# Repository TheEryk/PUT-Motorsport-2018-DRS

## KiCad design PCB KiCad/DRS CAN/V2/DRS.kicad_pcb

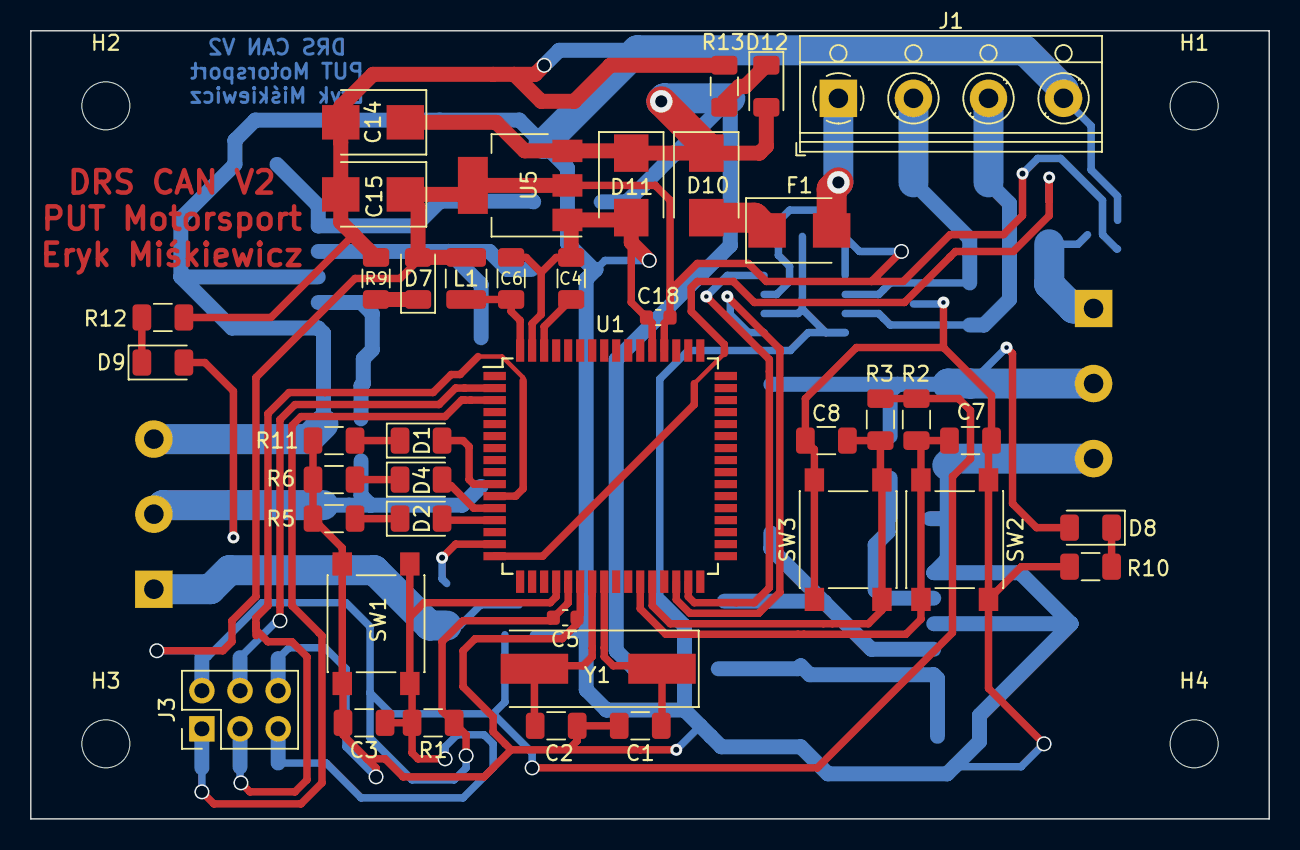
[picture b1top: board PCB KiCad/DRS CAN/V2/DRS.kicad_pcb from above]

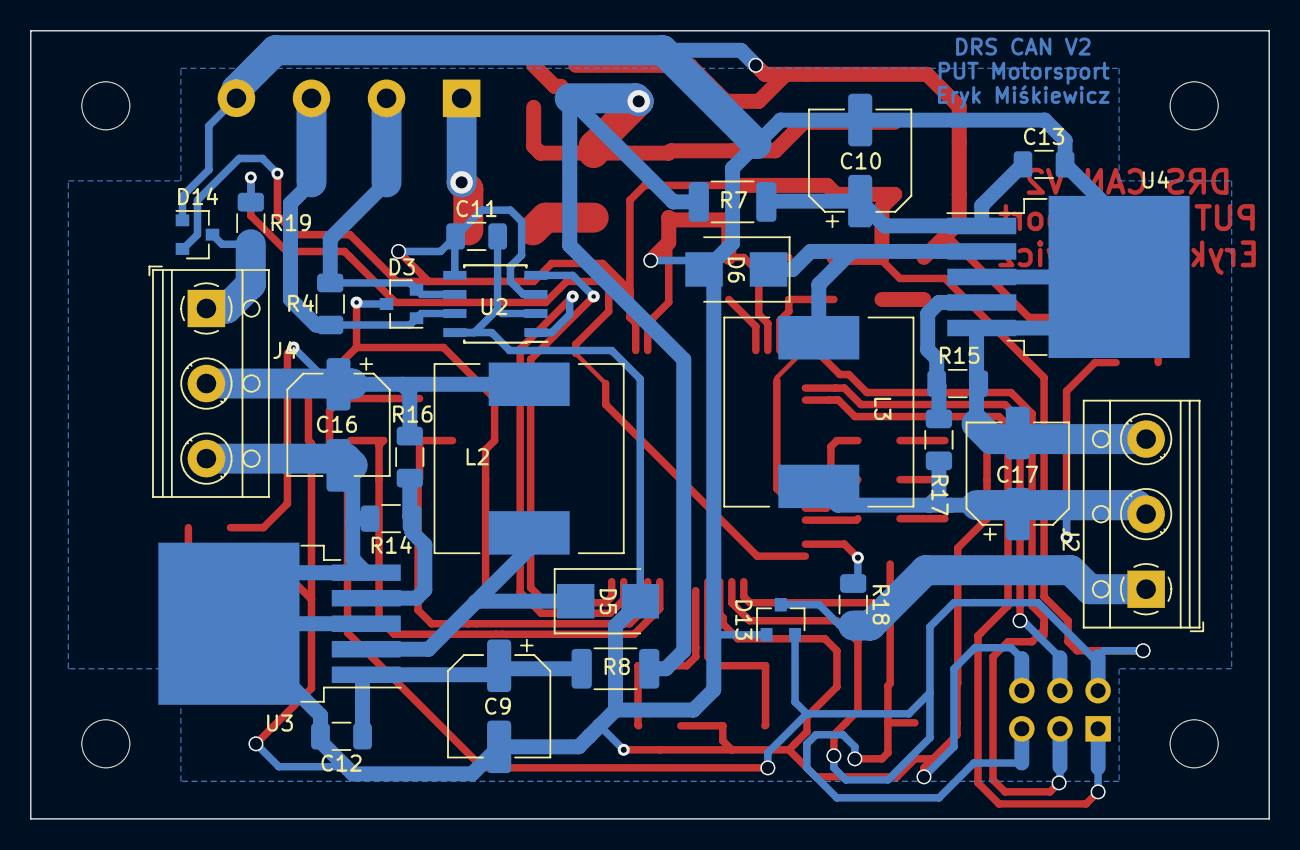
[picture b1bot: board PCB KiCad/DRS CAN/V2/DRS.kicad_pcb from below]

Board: 2 copper layers, 82.5 x 52.5 mm, 72 parts (28 on the bottom side), 41 nets.

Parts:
C1, C2: 22p; C_1206_3216Metric
C3, C4, C6, C7, C8, C11, C12, C13: 100n; C_1206_3216Metric
C5, C18: 100n; C_0603_1608Metric
C9, C10: 100u; CP_Elec_6.3x7.7
C14, C15: CP; D_SMB
C16, C17: 220u; CP_Elec_6.3x7.7
D1, D2, D4, D7, D8, D9, D12: LED; LED_1206_3216Metric
D3: D_TVS_x2_AAC; SOT-23
D5, D6, D10: D_Schottky; D_SMB
D11: D_Zener; D_SMB
D13, D14: BAT54S; SOT-23
F1: Fuse; D_SMB
H1, H2, H3, H4: MountingHole; MountingHole_3.2mm_M3
J1: Screw_Terminal_01x04; TerminalBlock_RND_205-00014_1x04_P5.00mm_Horizontal
J2, J4: Screw_Terminal_01x03; TerminalBlock_RND_205-00013_1x03_P5.00mm_Horizontal
J3: Conn_02x03_Odd_Even; PinHeader_2x03_P2.54mm_Vertical
L1: 10u; L_1210_3225Metric
L2, L3: 33u; L_12x12mm_H8mm
R1, R2, R3: 10k; R_1206_3216Metric
R4: R_Small; R_1206_3216Metric
R5, R6, R9, R10, R11, R12: 330; R_1206_3216Metric
R7, R8: 0R; R_2010_5025Metric
R13: 2k; R_1206_3216Metric
R14, R15, R16, R17: 0R; R_1206_3216Metric
R18, R19: 1k; R_1206_3216Metric
SW1, SW2, SW3: SW_Push; SW_SPST_PTS645
U1: AT90CAN32-16AU; TQFP-64_14x14mm_P0.8mm
U2: MCP2562-E-SN; SOIC-8_3.9x4.9mm_P1.27mm
U3, U4: AP1501-K5G-13; TO-263-5_TabPin3
U5: LM1117-5.0; SOT-223-3_TabPin2
Y1: Crystal; Crystal_SMD_HC49-SD

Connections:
+5V: C5.2, C11.1, C15.1, C18.2, D7.2, D13.2, D14.2, J3.2, L1.1, R1.1, R2.1, R3.1, U1.21, U1.52, U2.3, U2.5, U5.2
+5VL: C17.1, D9.2, J2.2, L3.2, R17.2
+5VP: C16.1, D8.2, J4.2, L2.2, R16.2
+12P: F1.2, J1.1
+12V: C14.1, D10.1, D11.1, D12.2, R7.2, R8.2, U5.3
/Button1: C7.2, R2.2, SW2.2, U1.27
/Button2: C8.2, R3.2, SW3.2, U1.28
/CANH: D3.1, J1.3, R4.1, U2.7
/CANL: D3.2, J1.2, R4.2, U2.6
/LED1: D1.2, U1.10
/LED2: D4.2, U1.12
/LED3: D2.2, U1.13
/MISO: J3.1, U1.3
/MOSI: J3.4, U1.2
/PWM1: R18.1, U1.15
/PWM2: R19.1, U1.16
/RESET: C3.1, J3.5, R1.2, SW1.2, U1.20
/RXCAN: U1.31, U2.4
/SCK: J3.3, U1.11
/TXCAN: U1.30, U2.1
/Zasilanie/5LU: D6.1, L3.1, U4.2
/Zasilanie/5PU: D5.1, L2.1, U3.2
/Zasilanie/12L: C10.1, C13.1, R7.1, U4.1
/Zasilanie/12P: C9.1, C12.1, R8.1, U3.1
/Złącza/PWM1Out: D13.3, J2.1, R18.2
/Złącza/PWM2Out: D14.3, J4.1, R19.2
GND: C1.2, C2.2, C3.2, C4.2, C5.1, C6.1, C7.1, C8.1, C9.2, C10.2, C11.2, C12.2, C13.2, C14.2, C15.2, C16.2, C17.2, C18.1, D3.3, D5.2, D6.2, D11.2, D13.1, D14.1, J1.4, J2.3, J3.6, J4.3, R5.2, R6.2, R9.2, R10.2, R11.2, R12.2, R13.2, R14.1, R15.1, SW1.1, SW2.1, SW3.1, U1.22, U1.53, U1.63, U2.2, U2.8, U3.3, U3.5, U4.3, U4.5, U5.1
unnamed: C1.1, U1.24, Y1.1
unnamed: C2.1, U1.23, Y1.2
unnamed: C4.1, U1.62
unnamed: C6.2, L1.2, U1.64
unnamed: D1.1, R11.1
unnamed: D2.1, R5.1
unnamed: D4.1, R6.1
unnamed: D7.1, R9.1
unnamed: D8.1, R10.1
unnamed: D9.1, R12.1
unnamed: D10.2, F1.1
unnamed: D12.1, R13.1
unnamed: R14.2, R16.1, U3.4
unnamed: R15.2, R17.1, U4.4

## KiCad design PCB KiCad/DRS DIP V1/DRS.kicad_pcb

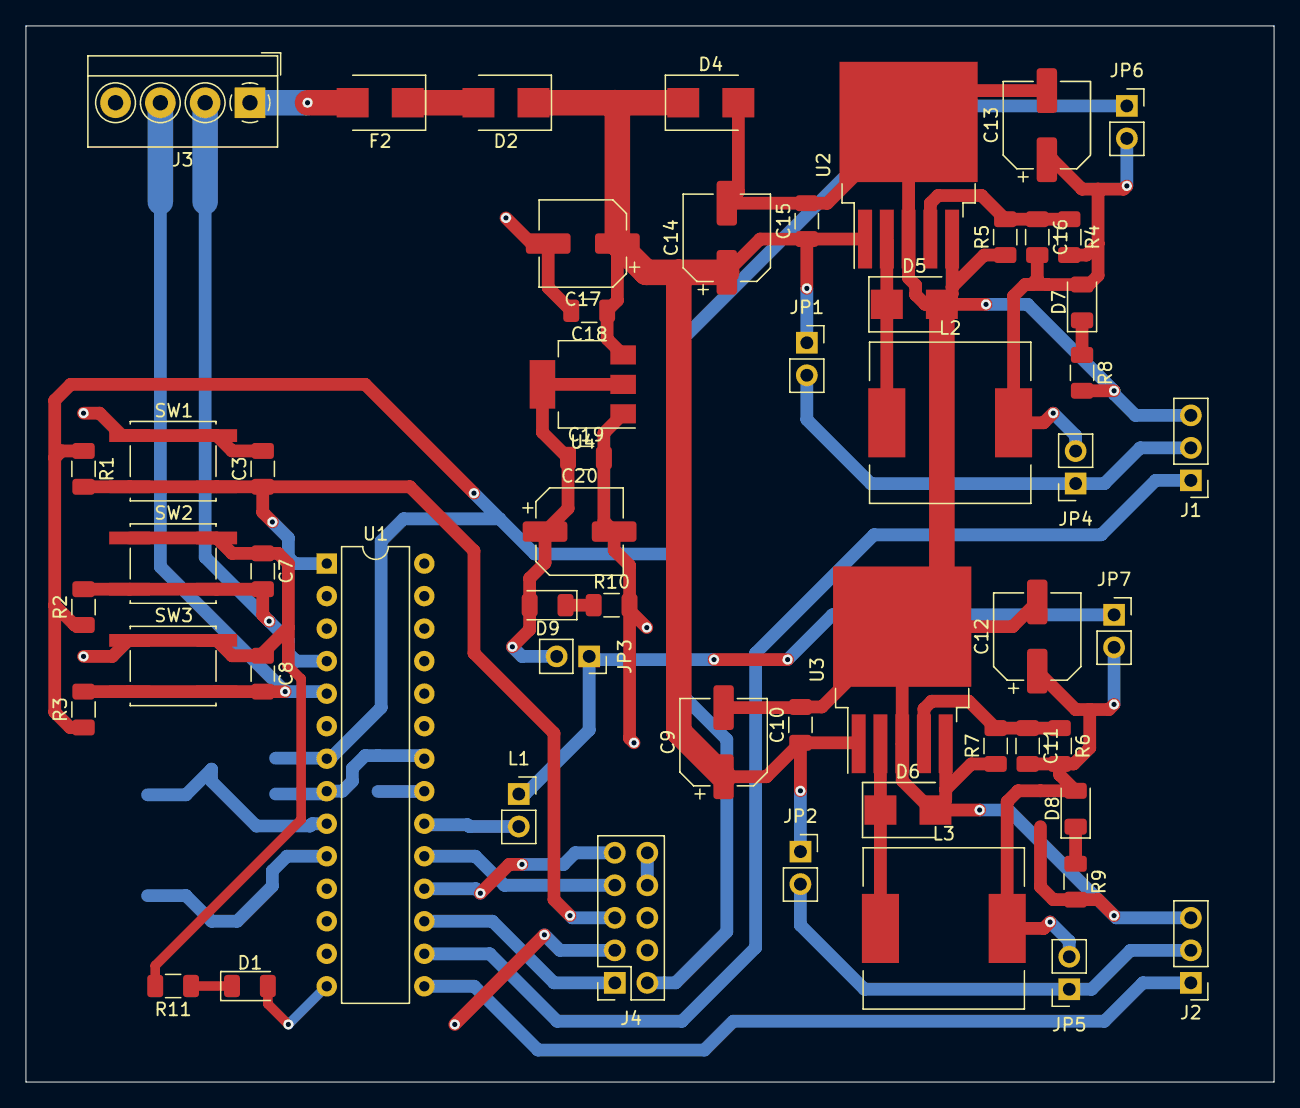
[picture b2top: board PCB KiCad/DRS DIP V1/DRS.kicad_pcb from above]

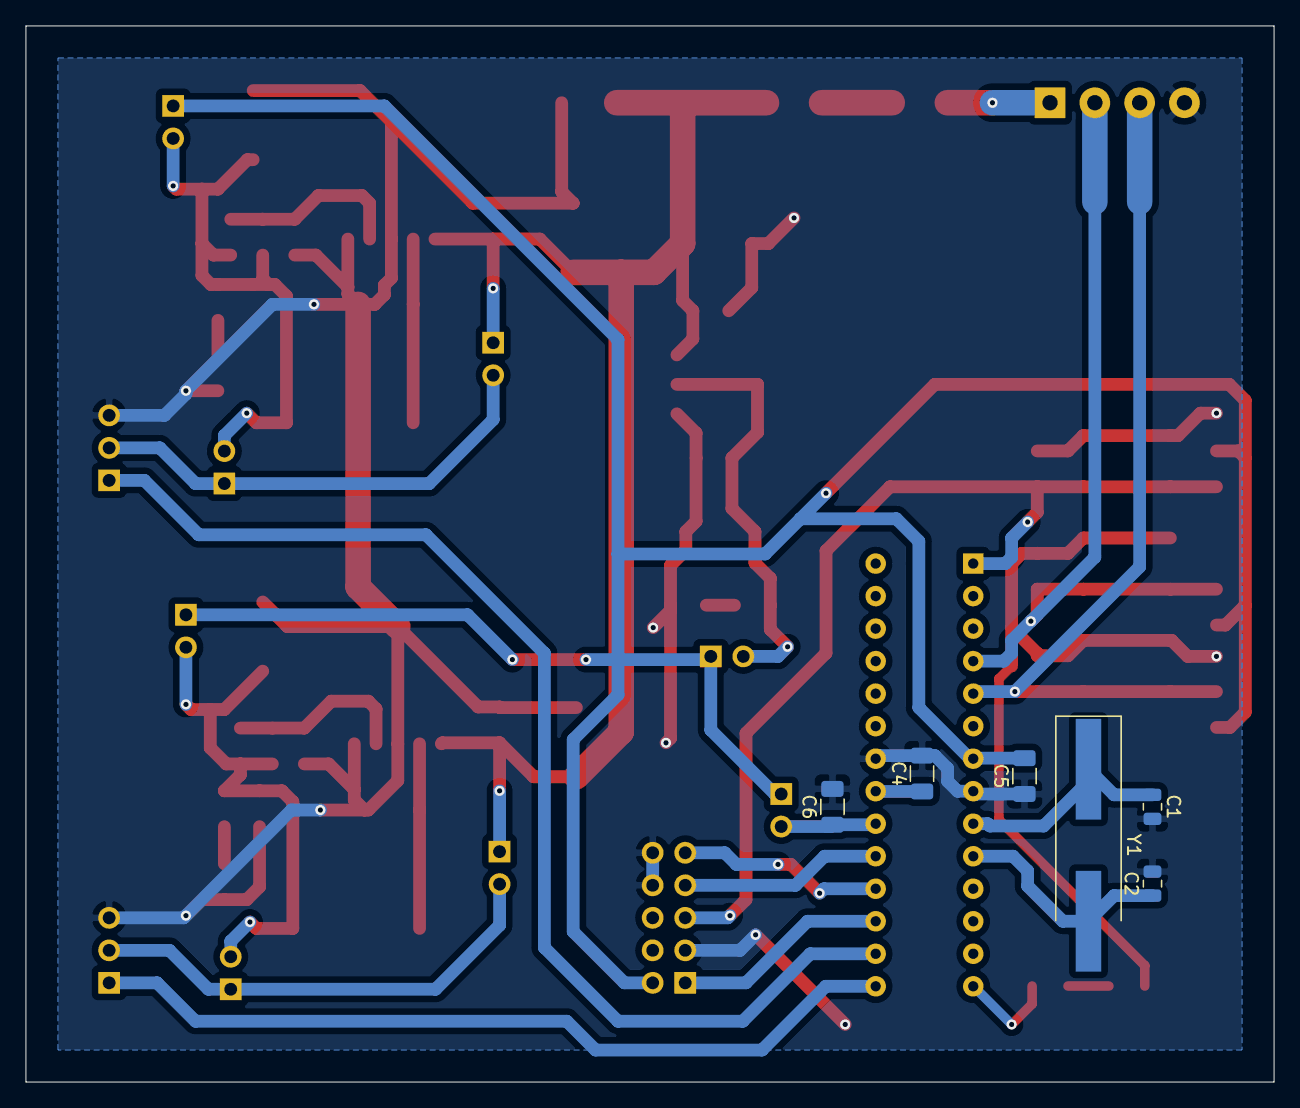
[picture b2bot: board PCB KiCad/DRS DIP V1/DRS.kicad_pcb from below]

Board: 2 copper layers, 97.5 x 82.5 mm, 62 parts (6 on the bottom side), 31 nets.

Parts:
C1, C2: 22p; C_0805_2012Metric
C3, C4, C5, C6, C7, C8, C10, C15, C18, C19: 100n; C_1206_3216Metric
C9, C14, C17, C20: 100u; CP_Elec_6.3x7.7
C11, C16: 20n; C_1206_3216Metric
C12, C13: 470u/220u; CP_Elec_6.3x7.7
D1, D7, D8, D9: LED; LED_1206_3216Metric
D2: D_Schottky; D_SMB
D4, D5, D6: D_Zener; D_SMB
F2: Fuse; D_SMB
J1: Jp7; PinHeader_1x03_P2.54mm_Vertical
J2: Jp8; PinHeader_1x03_P2.54mm_Vertical
J3: Jp8; TerminalBlock_4Ucon_1x04_P3.50mm_Horizontal
J4: Conn_02x05_Odd_Even; PinSocket_2x05_P2.54mm_Vertical
JP1: Jp6; PinSocket_1x02_P2.54mm_Vertical
JP2, JP3: Jp3; PinSocket_1x02_P2.54mm_Vertical
JP4: Jp4; PinSocket_1x02_P2.54mm_Vertical
JP5: Jp1; PinSocket_1x02_P2.54mm_Vertical
JP6: Jp5; PinSocket_1x02_P2.54mm_Vertical
JP7: Jp2; PinSocket_1x02_P2.54mm_Vertical
L1: 10u; PinSocket_1x02_P2.54mm_Vertical
L2, L3: 33u; L_12x12mm_H8mm
R1: 10k; R_1206_3216Metric
R2, R3, R4, R5, R6, R7: R; R_1206_3216Metric
R8, R9, R10, R11: 330; R_1206_3216Metric
SW1, SW2, SW3: SW_Push; SW_SPST_EVQQ2
U1: ATmega8-16PU; DIP-28_W7.62mm
U2, U3: LM2596S-ADJ; TO-263-5_TabPin3
U4: LM1117-5.0; SOT-223-3_TabPin2
Y1: Crystal; Crystal_SMD_HC49-SD_HandSoldering

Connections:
+5V: C5.2, J4.2, JP3.1, JP6.1, JP7.1, L1.1, R1.1, R2.1, R3.1, U1.7
+12P: C9.1, C10.1, C14.1, C15.1, C17.1, C18.1, D2.1, D4.1, JP1.1, JP2.1, U2.1, U3.1, U4.3
+12V: F2.2, J3.1
/Button1: C7.2, J3.2, R2.2, SW2.2, U1.4
/Button2: C8.2, J3.3, R3.2, SW3.2, U1.5
/LED: D1.2, U1.14
/MISO: J4.9, U1.18
/MOSI: J4.1, U1.17
/PWM1: J2.1, U1.15
/PWM2: J1.1, U1.16
/RESET: C3.1, J4.5, R1.2, SW1.2, U1.1
/SCK: J4.7, U1.19
GND: C1.2, C2.2, C3.2, C4.2, C5.1, C6.2, C7.1, C8.1, C9.2, C10.2, C12.2, C13.2, C14.2, C15.2, C17.2, C18.2, C19.2, C20.2, D4.2, D5.2, D6.2, J1.3, J2.3, J3.4, J4.3, J4.8, J4.10, R5.1, R7.1, R8.2, R9.2, R10.2, R11.2, SW1.1, SW2.1, SW3.1, U1.8, U1.22, U2.3, U2.5, U3.3, U3.5, U4.1
unnamed: C1.1, U1.9, Y1.1
unnamed: C2.1, U1.10, Y1.2
unnamed: C4.1, U1.21
unnamed: C6.1, L1.2, U1.20
unnamed: C11.1, R6.1, R7.2, U3.4
unnamed: C11.2, C12.1, D8.2, JP5.2, JP7.2, L3.2, R6.2
unnamed: C13.1, C16.2, D7.2, JP4.2, JP6.2, L2.2, R4.2
unnamed: C16.1, R4.1, R5.2, U2.4
unnamed: C19.1, C20.1, D9.2, JP3.2, U4.2
unnamed: D1.1, R11.1
unnamed: D2.2, F2.1
unnamed: D5.1, L2.1, U2.2
unnamed: D6.1, L3.1, U3.2
unnamed: D7.1, R8.1
unnamed: D8.1, R9.1
unnamed: D9.1, R10.1
VDD: J1.2, JP1.2, JP4.1
Vdrive: J2.2, JP2.2, JP5.1

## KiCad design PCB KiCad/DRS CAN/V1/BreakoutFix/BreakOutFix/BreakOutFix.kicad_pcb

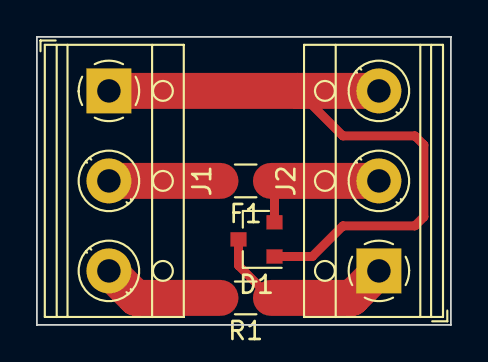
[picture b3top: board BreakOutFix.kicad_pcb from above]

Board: 2 copper layers, 23.0 x 16.0 mm, 5 parts (0 on the bottom side), 5 nets.

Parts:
D1: BAT54S; SOT-23
F1: Fuse; Fuse_1206_3216Metric
J1, J2: Screw_Terminal_01x03; TerminalBlock_RND_205-00013_1x03_P5.00mm_Horizontal
R1: R; R_1206_3216Metric

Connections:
+5V: D1.2, F1.1, J2.2
/PWM_IN: D1.3, J2.1, R1.1
/PWM_OUT: J1.3, R1.2
GND: D1.1, J1.1, J2.3
unnamed: F1.2, J1.2

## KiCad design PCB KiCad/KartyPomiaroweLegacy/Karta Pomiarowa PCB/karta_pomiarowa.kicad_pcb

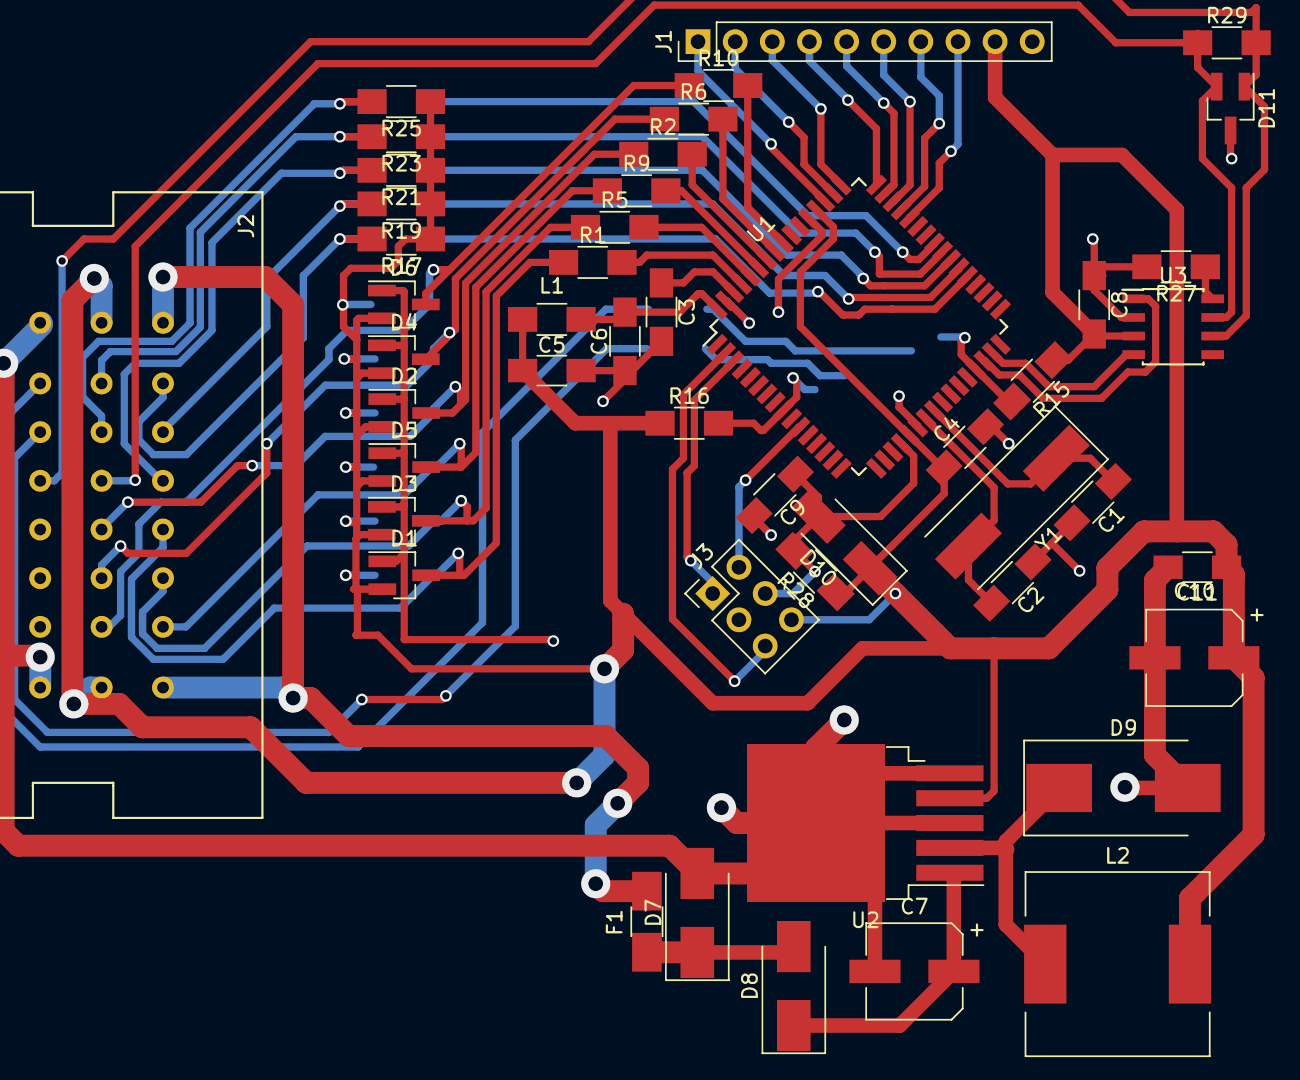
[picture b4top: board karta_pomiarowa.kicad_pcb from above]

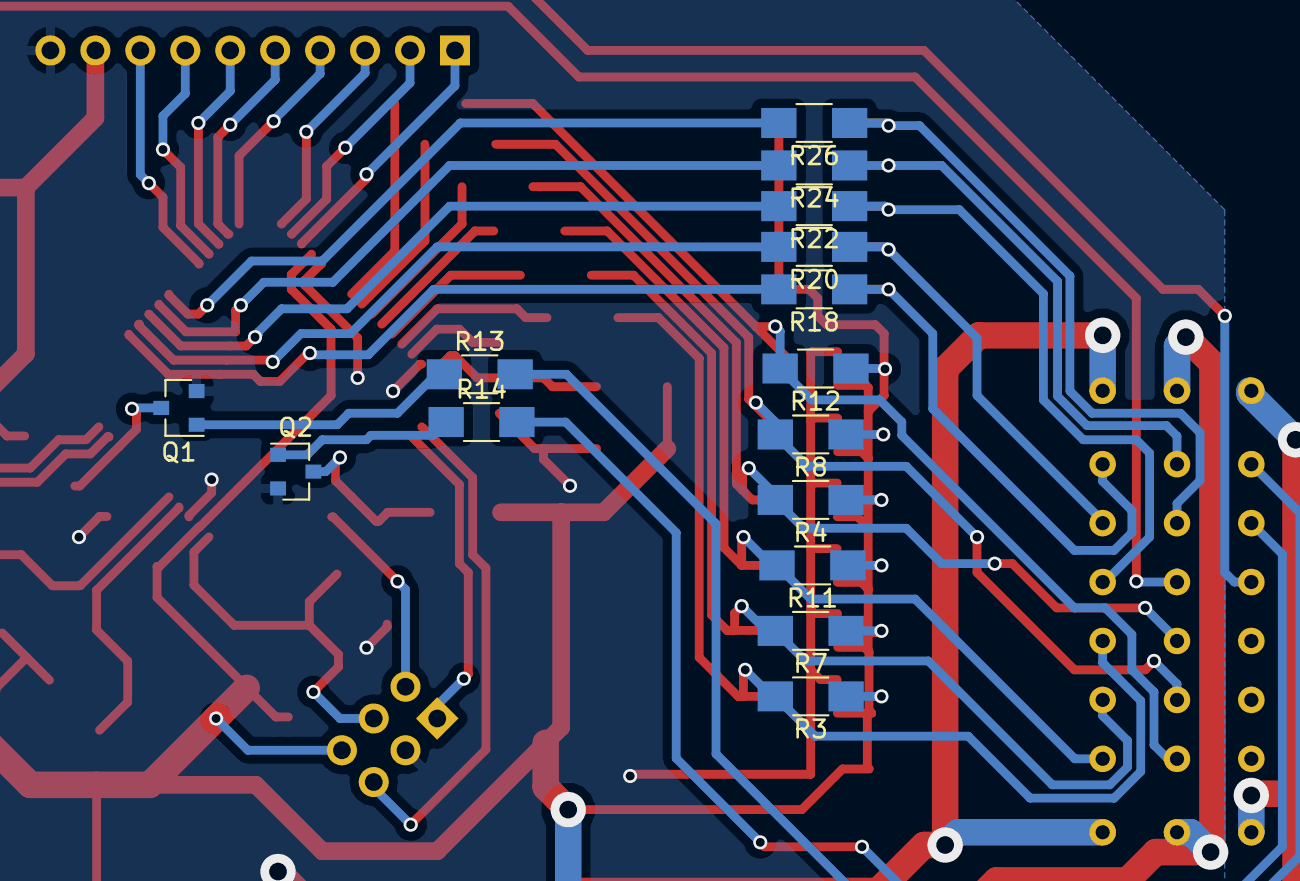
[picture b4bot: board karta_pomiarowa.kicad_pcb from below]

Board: 2 copper layers, 63 parts (15 on the bottom side), 55 nets.

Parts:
C1, C2: 22pF; C_1206_HandSoldering
C3, C4, C5, C6, C8, C9, C11: 100nF; C_1206_HandSoldering
C7: 470uF/16V; CP_Elec_6.3x7.7
C10: 100uF/6,3V; CP_Elec_6.3x5.8
D1, D2, D3, D4, D5, D6: BAT54S; SOT-23_Handsoldering
D7: SMBJ14CA; D_SMB_Handsoldering
D8: SS24; D_SMB_Handsoldering
D9: SS34; D_SMC_Handsoldering
D10: 1n4148; D_SMA_Handsoldering
D11: SM712; SOT-23_Handsoldering
F1: Fuse; Fuse_SMD1206_HandSoldering
J1: Conn_01x10; Pin_Header_Straight_1x10_Pitch2.54mm
J2: fci_connector_24pin
J3: Conn_02x03_Counter_Clockwise; Pin_Header_Straight_2x03_Pitch2.54mm
L1: 10uH; L_1206_HandSoldering
L2: 33uH/3A; L_12x12mm_h8mm
Q1, Q2: BC817; SOT-23
R1, R2, R5, R6, R9, R10: 470; R_1206_HandSoldering
R3, R4, R7, R8, R11, R12, R15, R16, R17, R19, R21, R23, R25, R28: 4k7; R_1206_HandSoldering
R13, R14: 2k7; R_1206_HandSoldering
R18, R20, R22, R24, R26: 100; R_1206_HandSoldering
R27: 10k; R_1206_HandSoldering
R29: 120; R_1206_HandSoldering
U1: AT90CAN32-16AU; TQFP-64_14x14mm_Pitch0.8mm
U2: LM2596S-5; TO-263-5_TabPin3
U3: MCP2551-I/SN; SOIC-8_3.9x4.9mm_Pitch1.27mm
Y1: 16MHz; Crystal_SMD_HC49-SD

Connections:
/+12: F1.2, J2.1, J2.8
/ANALOG1: R1.2, U1.61
/ANALOG1_IN: D1.3, J2.5, R1.1, R3.2
/ANALOG2: R5.2, U1.60
/ANALOG2_IN: D3.3, J2.6, R5.1, R7.2
/ANALOG3: R9.2, U1.59
/ANALOG3_IN: D5.3, J2.7, R9.1, R11.2
/ANALOG4: R2.2, U1.58
/ANALOG4_IN: D2.3, J2.13, R2.1, R4.2
/ANALOG5: R6.2, U1.57
/ANALOG5_IN: D4.3, J2.14, R6.1, R8.2
/ANALOG6: R10.2, U1.56
/ANALOG6_IN: D6.3, J2.15, R10.1, R12.2
/CANH: D11.2, J2.12, R29.1, U3.7
/CANL: D11.1, J2.20, R29.2, U3.6
/External_Analog0: J1.1, U1.51
/External_Analog1: J1.2, U1.50
/External_Analog2: J1.3, U1.49
/External_Analog3: J1.4, U1.48
/External_Analog4: J1.5, U1.47
/External_Analog5: J1.6, U1.46
/External_Analog6: J1.7, U1.45
/External_Analog7: J1.8, U1.44
/IND1: J2.18, R13.2
/IND2: J2.19, R14.2
/P1: R18.2, U1.37
/P1_IN: J2.2, R17.2, R18.1
/P2: R20.2, U1.38
/P2_IN: J2.3, R19.2, R20.1
/P3: R22.2, U1.39
/P3_IN: J2.4, R21.2, R22.1
/P4: R24.2, U1.40
/P4_IN: J2.10, R23.2, R24.1
/P5: R26.2, U1.41
/P5_IN: J2.11, R25.2, R26.1
/PDI: J3.5, U1.2
/PDO: J3.1, U1.3
/RESET: C9.1, D10.2, J3.4, R28.2, U1.20
/RXCAN: U1.31, U3.4
/SCK: J3.2, U1.11
/TIMER1: Q1.3, R15.2, U1.29
/TIMER3: Q2.3, R16.2, U1.9
/TXCAN: U1.30, U3.1
/VCC: C4.1, C5.1, C8.2, C10.1, C11.1, D1.2, D2.2, D3.2, D4.2, D5.2, D6.2, D10.1, J1.9, J2.9, J2.16, J3.6, L1.1, L2.2, R3.1, R4.1, R7.1, R8.1, R11.1, R12.1, R15.1, R16.1, R17.1, R19.1, R21.1, R23.1, R25.1, R28.1, U1.21, U1.52, U2.4, U3.3
GND: C1.2, C2.1, C3.2, C4.2, C5.2, C6.1, C7.2, C8.1, C9.2, C10.2, C11.2, D1.1, D2.1, D3.1, D4.1, D5.1, D6.1, D7.2, D9.2, D11.3, J1.10, J2.17, J2.24, J3.3, Q1.2, Q2.2, R27.2, U1.22, U1.53, U1.63, U2.3, U2.5, U3.2
unnamed: C1.1, U1.24, Y1.1
unnamed: C2.2, U1.23, Y1.2
unnamed: C3.1, U1.62
unnamed: C6.2, L1.2, U1.64
unnamed: C7.1, D8.1, U2.1
unnamed: D7.1, D8.2, F1.1
unnamed: D9.1, L2.1, U2.2
unnamed: Q1.1, R13.1
unnamed: Q2.1, R14.1
unnamed: R27.1, U3.8

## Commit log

2018-12-17 Pliki od Sneli
2019-04-12 FirstAndFinalXD
2019-04-14 04_14 CAN v1
2019-04-14 04_14 CANv2
2019-04-14 04_14 fix1
2019-04-24 04_24
2019-05-05 05_05
2019-05-05 05_05 v2
    Skończony projekt testowy na at90can
2019-05-07 05_08
2019-05-11 At90can v1
    Zaprojektowano nowe PCB na bolid
2019-05-12 DRS_receiver
2019-05-12 Code cleanup
2019-05-12 male zmiany
2019-05-12 Adjustable voltage fix
2019-05-13 cos tam nic duzego
2019-05-13 at8 fix
2019-05-16 ustawienie poczatkowej wartosci pwm, nalezy jeszcze ustawic odpowiednia czestotliwosc
2019-05-27 DRS_AT90CAN odbieranie poprawnej ramki sygnalizowane przelaczeniem diody na PB3
2019-05-31 Dodana funkcja PWM servo, przykladowa obsluga drs'u po Canie
2019-06-05 Dodano płytkę z zabezpieczeniem wyjść
2019-06-07 WersjaV2 PCB
2019-06-14 DZIALAJACY CAN 500KBits NA SYGNAL DRS PRZELACZA DIODY
2019-06-14 DZIALAJACY CAN 1MBits NA SYGNAL DRS PRZELACZA DIODY
2019-06-15 Jakies zmiany
2019-06-15 DRS state msg etc
2019-06-19 dziala DRS na ramkach Can
2019-06-27 Testy 27.06.2019, CAN 2 ramki - hamulca i przycisku
2019-06-28 DRS dziala, todo: ustalic ramke hamulca
2019-06-29 Updated brake's frame
2019-06-29 DRS is open when button is pushed and no brake
2019-06-29 DRS is open when button is pushed, closed when button is released, closed when braking, closed when CAN signal is lost
2019-07-01 Button from bit3 to bit2, good pwm vaules
2019-07-02 tested, good todo: set PWM values for drs assembly on car, add menu - easier pwm settings
2019-07-04 all good for ride'
2019-07-10 Final release(propably), drs mcu programmed - 10 07 2019 1:40:00
2019-07-17 pokretlo
2019-07-19 pokretlo 2.0 raczej ostateczne
